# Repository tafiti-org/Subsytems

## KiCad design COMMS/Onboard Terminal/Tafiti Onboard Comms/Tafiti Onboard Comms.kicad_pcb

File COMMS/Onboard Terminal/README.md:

# Tafiti Onboard Communication System

This is the PCB design of the Onboard communication system.

## Components
- STM32H743VIT6
- 2 x sx1278 Ra-02
- SD card module
- 2 x LEDs
- Switch

## Interfaces
- SDMMC
- CAN
- 2 x SPI
- JTAG

## Power Budget

## Schematic

## PCB layout

## 3D PCB Model

## Tools
- STM32CubeIDE
- KiCad

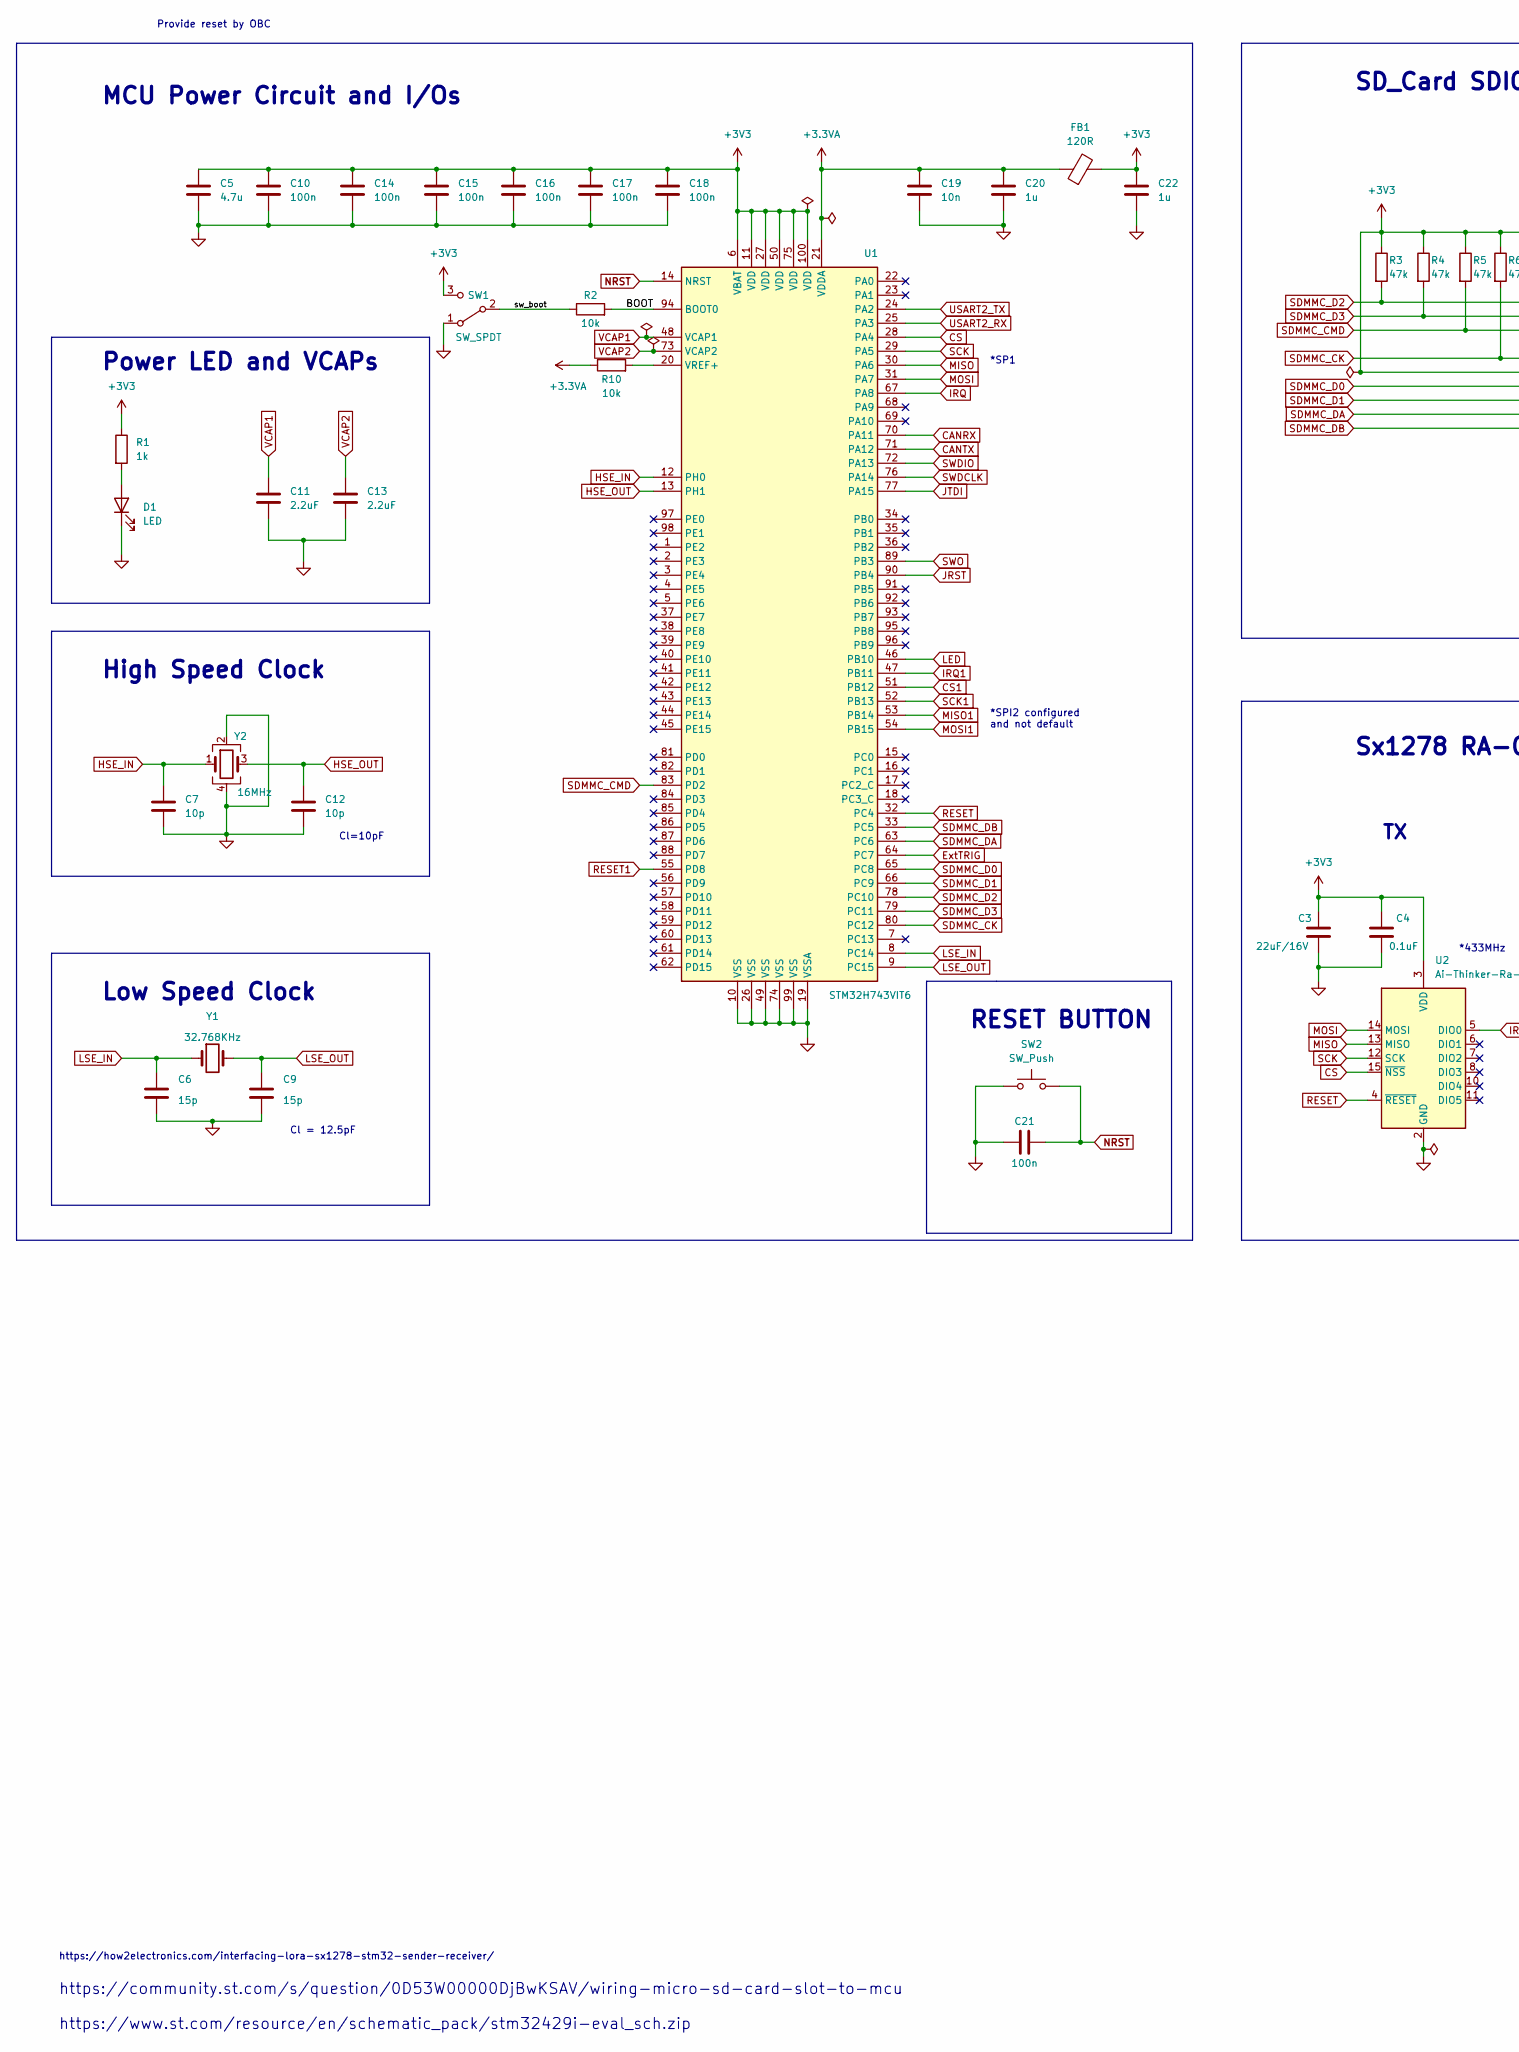
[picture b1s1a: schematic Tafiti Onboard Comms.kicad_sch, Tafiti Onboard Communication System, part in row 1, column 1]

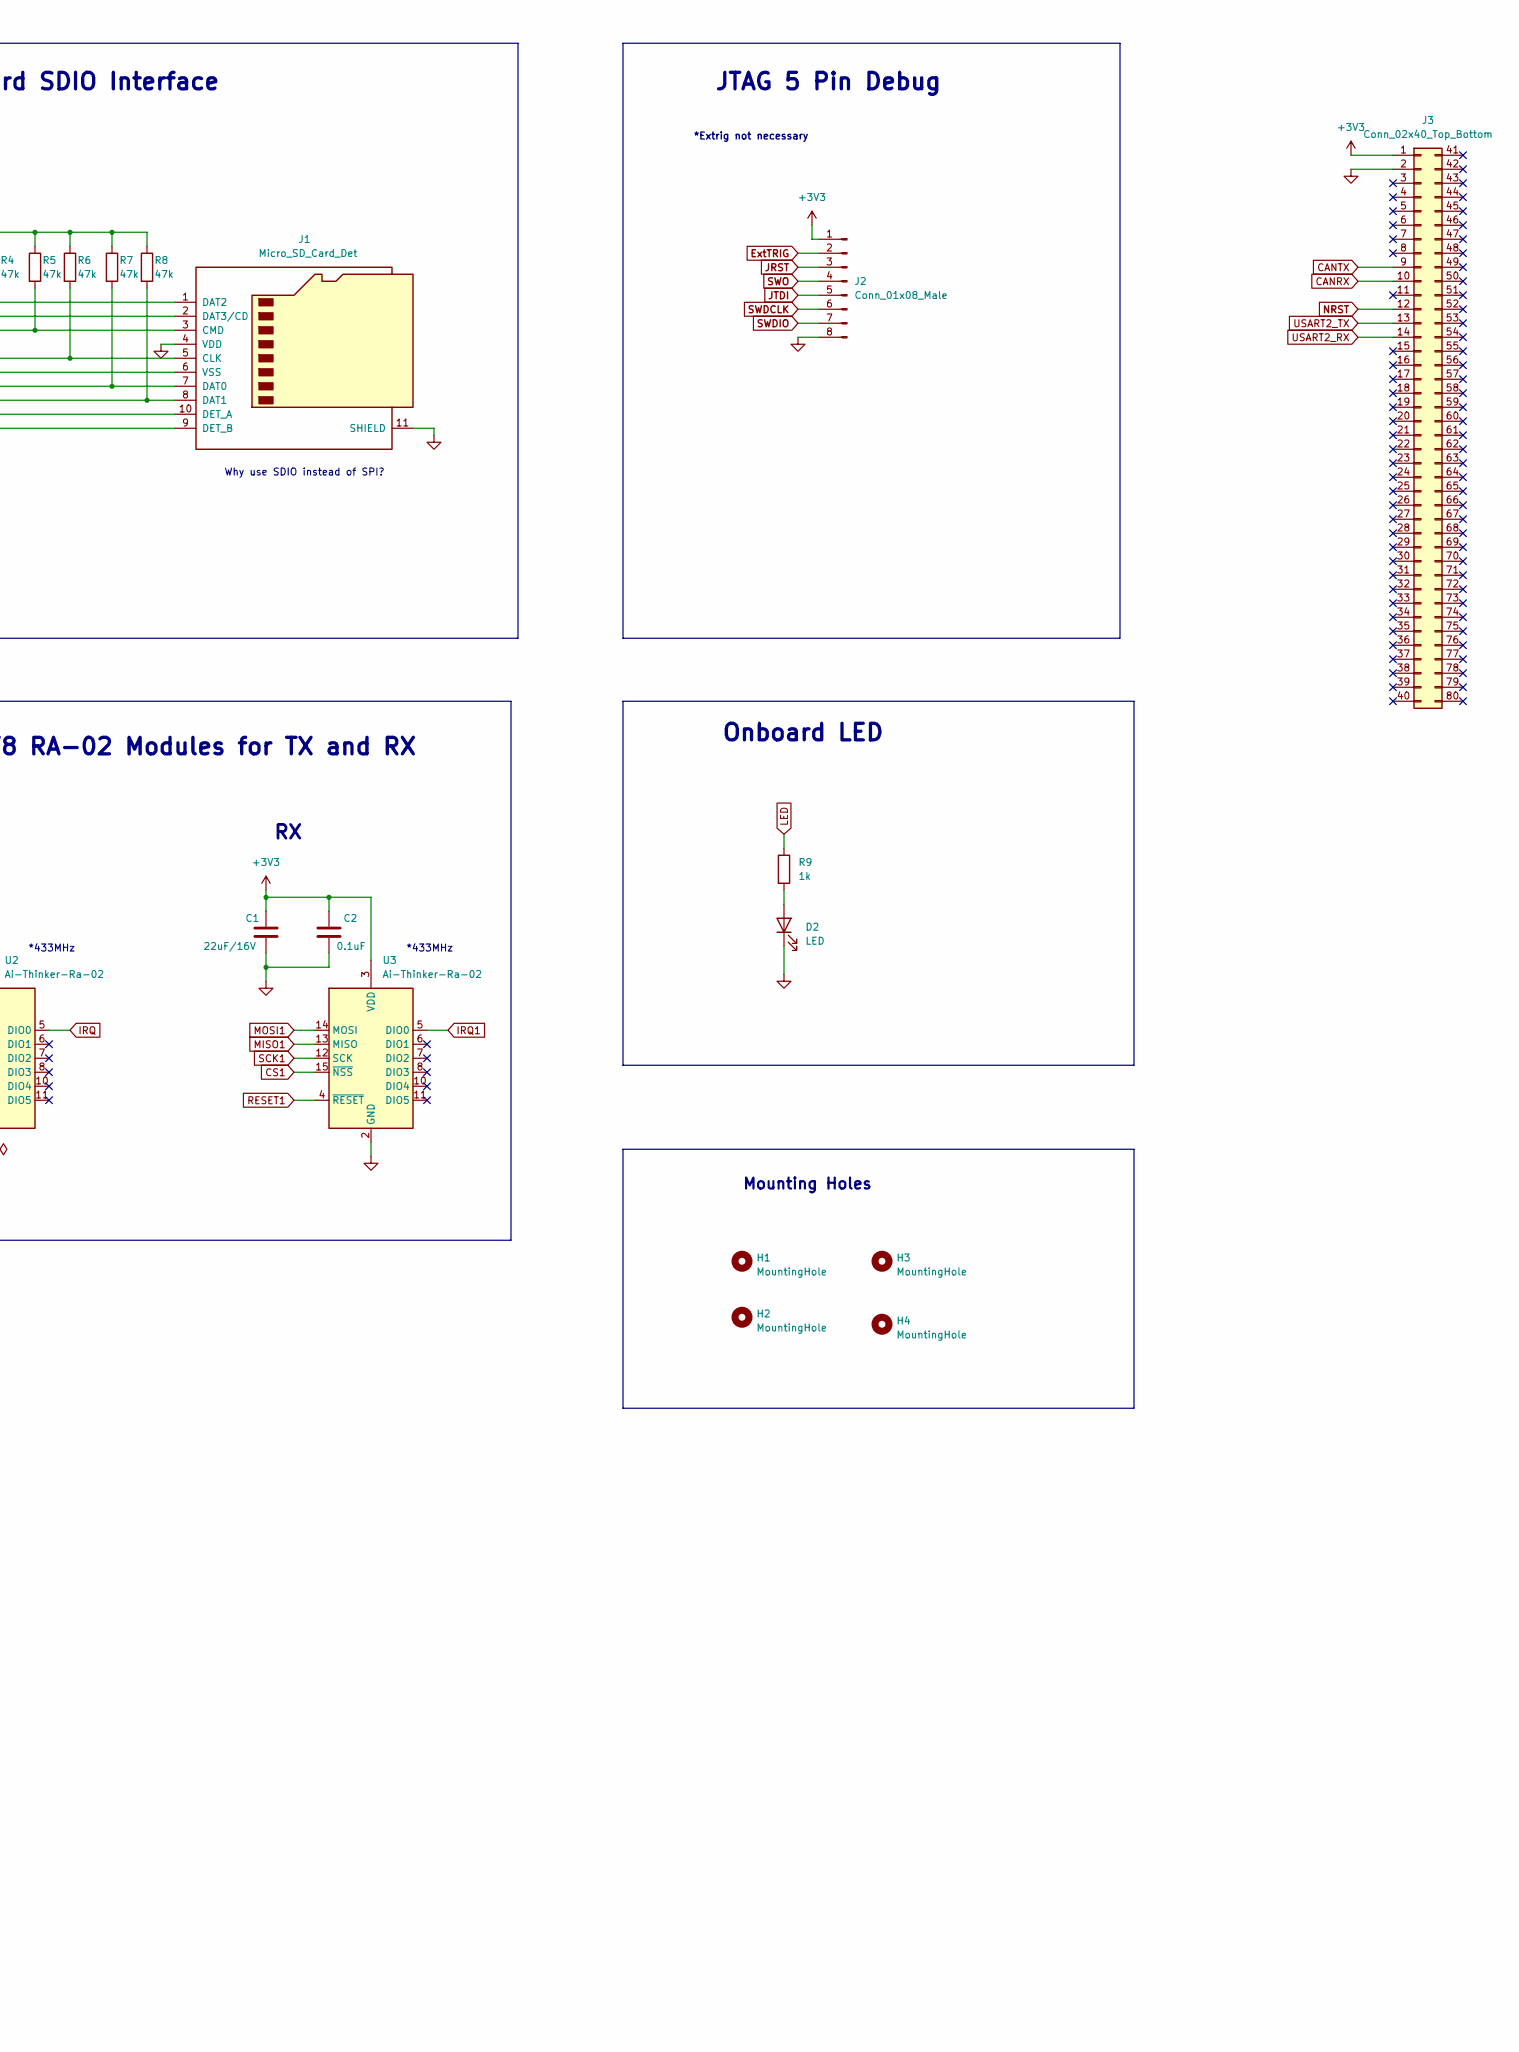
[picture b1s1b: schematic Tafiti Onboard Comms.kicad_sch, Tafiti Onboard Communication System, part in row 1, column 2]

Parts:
C1, C3: 22uF/16V; C_0603_1608Metric
C2, C4: 0.1uF; C_0402_1005Metric
C5: 4.7u; C_0603_1608Metric
C6, C9: 15p; C_0402_1005Metric
C7, C12: 10p; C_0402_1005Metric
C10, C14, C15, C16, C17, C18, C21: 100n; C_0402_1005Metric
C11: 2.2uF; C_0402_1005Metric
C13: 2.2uF; C_0603_1608Metric
C19: 10n; C_0402_1005Metric
C20, C22: 1u; C_0402_1005Metric
D1, D2: LED; LED_0603_1608Metric
FB1: 120R; L_0603_1608Metric
H1, H2, H3, H4: MountingHole
J1: Micro_SD_Card_Det; microSD_HC_Hirose_DM3D-SF
J2: Conn_01x08_Male; PinHeader_1x08_P2.54mm_Vertical
J3: Conn_02x40_Top_Bottom; PinSocket_2x40_P2.54mm_Vertical
R1, R9: 1k; R_0402_1005Metric
R2, R10: 10k; R_0402_1005Metric
R3, R4, R5, R6, R7, R8: 47k; R_0402_1005Metric
SW1: SW_SPDT; SW_E-Switch_EG1224_SPDT_Angled
SW2: SW_Push; SW_PUSH_6mm
U1: STM32H743VIT6; LQFP-100_14x14mm_P0.5mm
U2, U3: Ai-Thinker-Ra-02; Ai-Thinker-Ra-01-LoRa
Y1: 32.768KHz; Crystal_SMD_2012-2Pin_2.0x1.2mm
Y2: 16MHz; Crystal_SMD_3225-4Pin_3.2x2.5mm

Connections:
+3.3VA: C19.1, C20.1, FB1.1, R10.1, U1.21 (VDDA)
+3V3: C1.1, C2.1, C3.1, C4.1, C5.1, C10.1, C14.1, C15.1, C16.1, C17.1, C18.1, C22.1, FB1.2, J1.6 (VSS), J2.1, J3.1, R1.1, R3.1, R4.1, R5.1, R6.1, R7.1, R8.1, SW1.3 (C), U1.6 (VBAT), U1.11 (VDD), U1.27 (VDD), U1.50 (VDD), U1.75 (VDD), U1.100 (VDD), U2.3 (VDD), U3.3 (VDD)
/BOOT: R2.2, U1.94 (BOOT0)
/sw_boot: R2.1, SW1.2 (B)
CANRX: J3.10, U1.70 (PA11)
CANTX: J3.9, U1.71 (PA12)
CS: U1.28 (PA4), U2.15 (~NSS)
CS1: U1.51 (PB12), U3.15 (~NSS)
ExtTRIG: J2.2, U1.64 (PC7)
GND: C1.2, C2.2, C3.2, C4.2, C5.2, C6.2, C7.2, C9.2, C10.2, C11.2, C12.2, C13.2, C14.2, C15.2, C16.2, C17.2, C18.2, C19.2, C20.2, C21.1, C22.2, D1.1 (K), D2.1 (K), J1.4 (VDD), J1.11 (SHIELD), J2.8, J3.2, SW1.1 (A), SW2.1, U1.10 (VSS), U1.19 (VSSA), U1.26 (VSS), U1.49 (VSS), U1.74 (VSS), U1.99 (VSS), U2.1 (GND), U2.2 (GND), U2.9 (GND), U2.16 (GND), U3.1 (GND), U3.2 (GND), U3.9 (GND), U3.16 (GND), Y2.2, Y2.4
HSE_IN: C7.1, U1.12 (PH0), Y2.1
HSE_OUT: C12.1, U1.13 (PH1), Y2.3
IRQ: U1.67 (PA8), U2.5 (DIO0)
IRQ1: U1.47 (PB11), U3.5 (DIO0)
JRST: J2.3, U1.90 (PB4)
JTDI: J2.5, U1.77 (PA15)
LED: R9.1, U1.46 (PB10)
LSE_IN: C6.1, U1.8 (PC14), Y1.1
LSE_OUT: C9.1, U1.9 (PC15), Y1.2
MISO: U1.30 (PA6), U2.13 (MISO)
MISO1: U1.53 (PB14), U3.13 (MISO)
MOSI: U1.31 (PA7), U2.14 (MOSI)
MOSI1: U1.54 (PB15), U3.14 (MOSI)
NRST: C21.2, J3.12, SW2.2, U1.14 (NRST)
unnamed: D1.2 (A), R1.2
unnamed: D2.2 (A), R9.2
unnamed: R10.2, U1.20 (VREF+)
RESET: U1.32 (PC4), U2.4 (~RESET)
RESET1: U1.55 (PD8), U3.4 (~RESET)
SCK: U1.29 (PA5), U2.12 (SCK)
SCK1: U1.52 (PB13), U3.12 (SCK)
SDMMC_CK: J1.5 (CLK), R6.2, U1.80 (PC12)
SDMMC_CMD: J1.3 (CMD), R5.2, U1.83 (PD2)
SDMMC_D0: J1.7 (DAT0), R7.2, U1.65 (PC8)
SDMMC_D1: J1.8 (DAT1), R8.2, U1.66 (PC9)
SDMMC_D2: J1.1 (DAT2), R3.2, U1.78 (PC10)
SDMMC_D3: J1.2 (DAT3/CD), R4.2, U1.79 (PC11)
SDMMC_DA: J1.10 (DET_A), U1.63 (PC6)
SDMMC_DB: J1.9 (DET_B), U1.33 (PC5)
SWDCLK: J2.6, U1.76 (PA14)
SWDIO: J2.7, U1.72 (PA13)
SWO: J2.4, U1.89 (PB3)
USART2_RX: J3.14, U1.25 (PA3)
USART2_TX: J3.13, U1.24 (PA2)
VCAP1: C11.1, U1.48 (VCAP1)
VCAP2: C13.1, U1.73 (VCAP2)

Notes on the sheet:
Onboard LED
Cl = 12.5pF
Cl=10pF
https://www.st.com/resource/en/schematic_pack/stm32429i-eval_sch.zip
https://community.st.com/s/question/0D53W00000DjBwKSAV/wiring-micro-sd-card-slot-to-mcu
Mounting Holes
RESET BUTTON
*Extrig not necessary
Sx1278 RA-02 Modules for TX and RX
https://how2electronics.com/interfacing-lora-sx1278-stm32-sender-receiver/
JTAG 5 Pin Debug
*433MHz
Provide reset by OBC
Power LED and VCAPs
High Speed Clock
MCU Power Circuit and I/Os
Why use SDIO instead of SPI?
*SP1
*SPI2 configured and not default
Low Speed Clock
SD_Card SDIO Interface

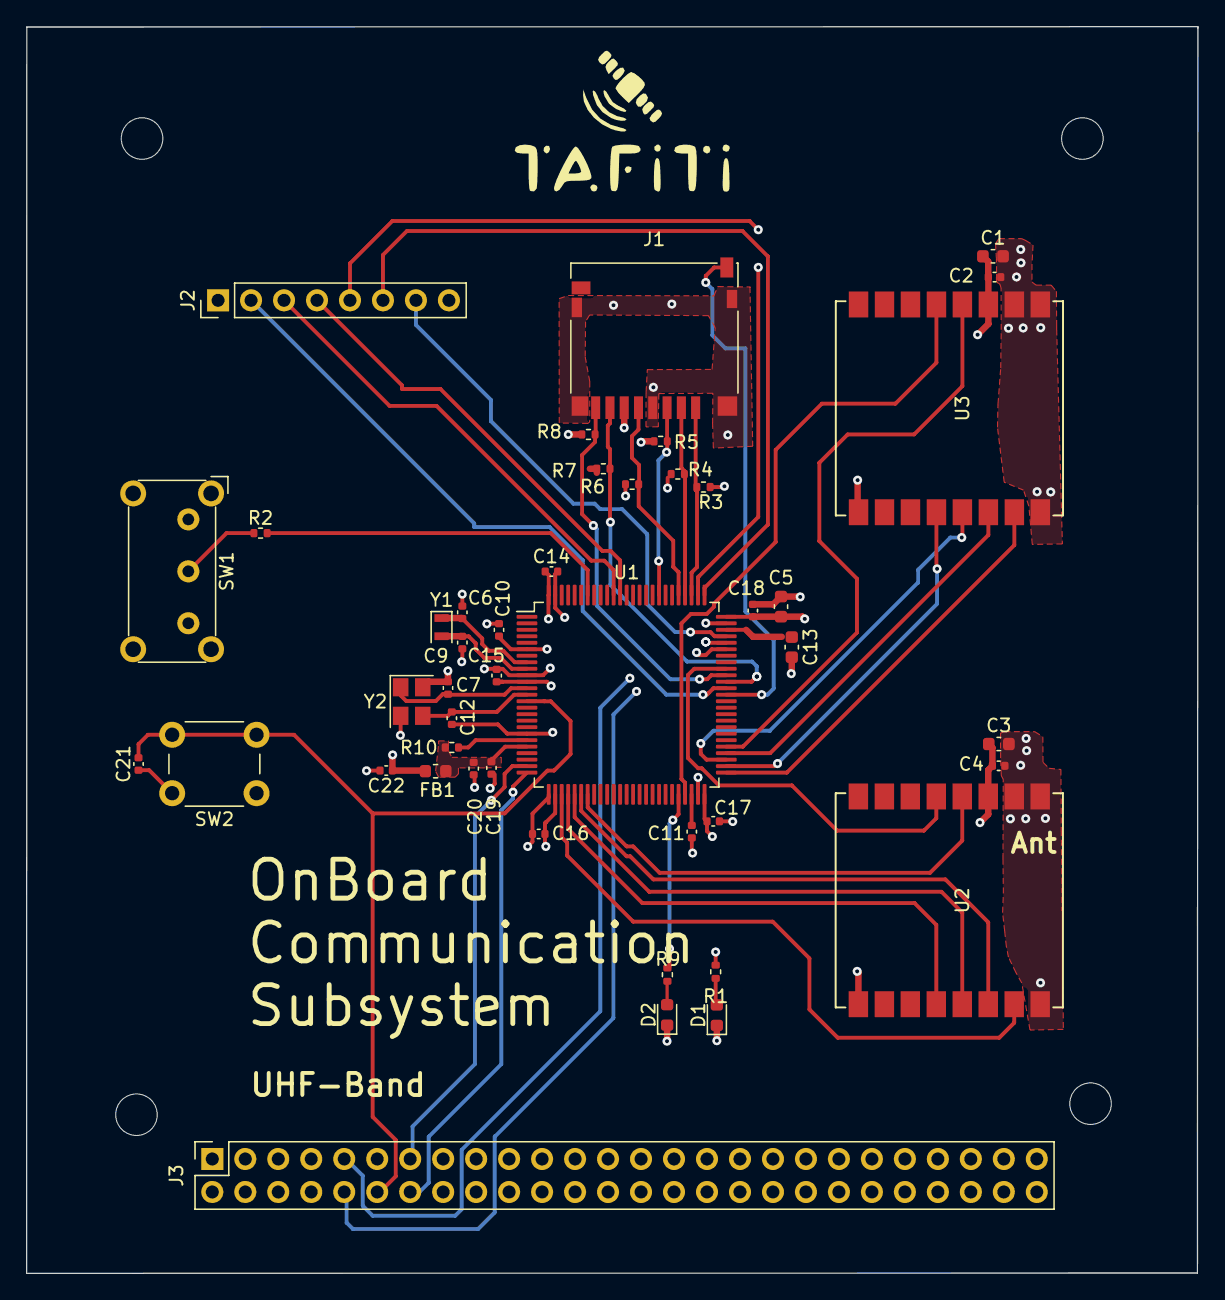
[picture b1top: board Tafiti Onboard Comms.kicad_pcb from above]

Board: 4 copper layers, 90.2 x 96.0 mm, 48 parts (0 on the bottom side), 46 nets.

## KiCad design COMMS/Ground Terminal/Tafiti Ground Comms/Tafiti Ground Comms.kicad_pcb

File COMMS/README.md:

# Tafiti Comms System

This is the repo containing contents of the Tafiti Communication System. This system is built under the sponsorship of the Kenya Space Agency.

## Work Still to be done
- Adding PC104 Connectors and assigned pins from main bus.
- Adding 3D models of the sx1278 Ra-02.
- Adding Logo, Subsytem name, members and more information
- Verify accuracy and requirements fulfilment
- Confirm that the PCB meets the EMC and EMI standards and that it is well designed.

(The above tasks should be done and marked as done beside the task)

## Meet the Team
- Gerald Mbuthia
- Anna kamene
- Martin Kibisu
- Timothy Ndichu
- Ezra Kanana
- Daph Peres

## Purpose

To provide a communication channel to transfer data to and from the Tafiti Nano-satellite.
The data to be transferred includes:
- Image data
- Housekeeping data
- Commands

## Requirements
- Receive housekeeping data from the OBC. This data will effectively be a collection of data from all other subsystems.
- Receive payload data from the Payload subsystem.
- Provide a communication link for the transfer of housekeeping data and payload data from the Cubesat to the 
ground terminal. 
- Provide a link to send telecommands from the ground to the cubesat. This will be a bi-directional communication.
- Provide an interface to view received data and key in commands.
- Allow for data storage onboard the cubesat and on the ground station.
- Provide an API to transfer data over Web.
- Should be portable.
- Data transfer rates should be fast.
- Long range.
## Development procedure

## Software Development

## Testing and Data

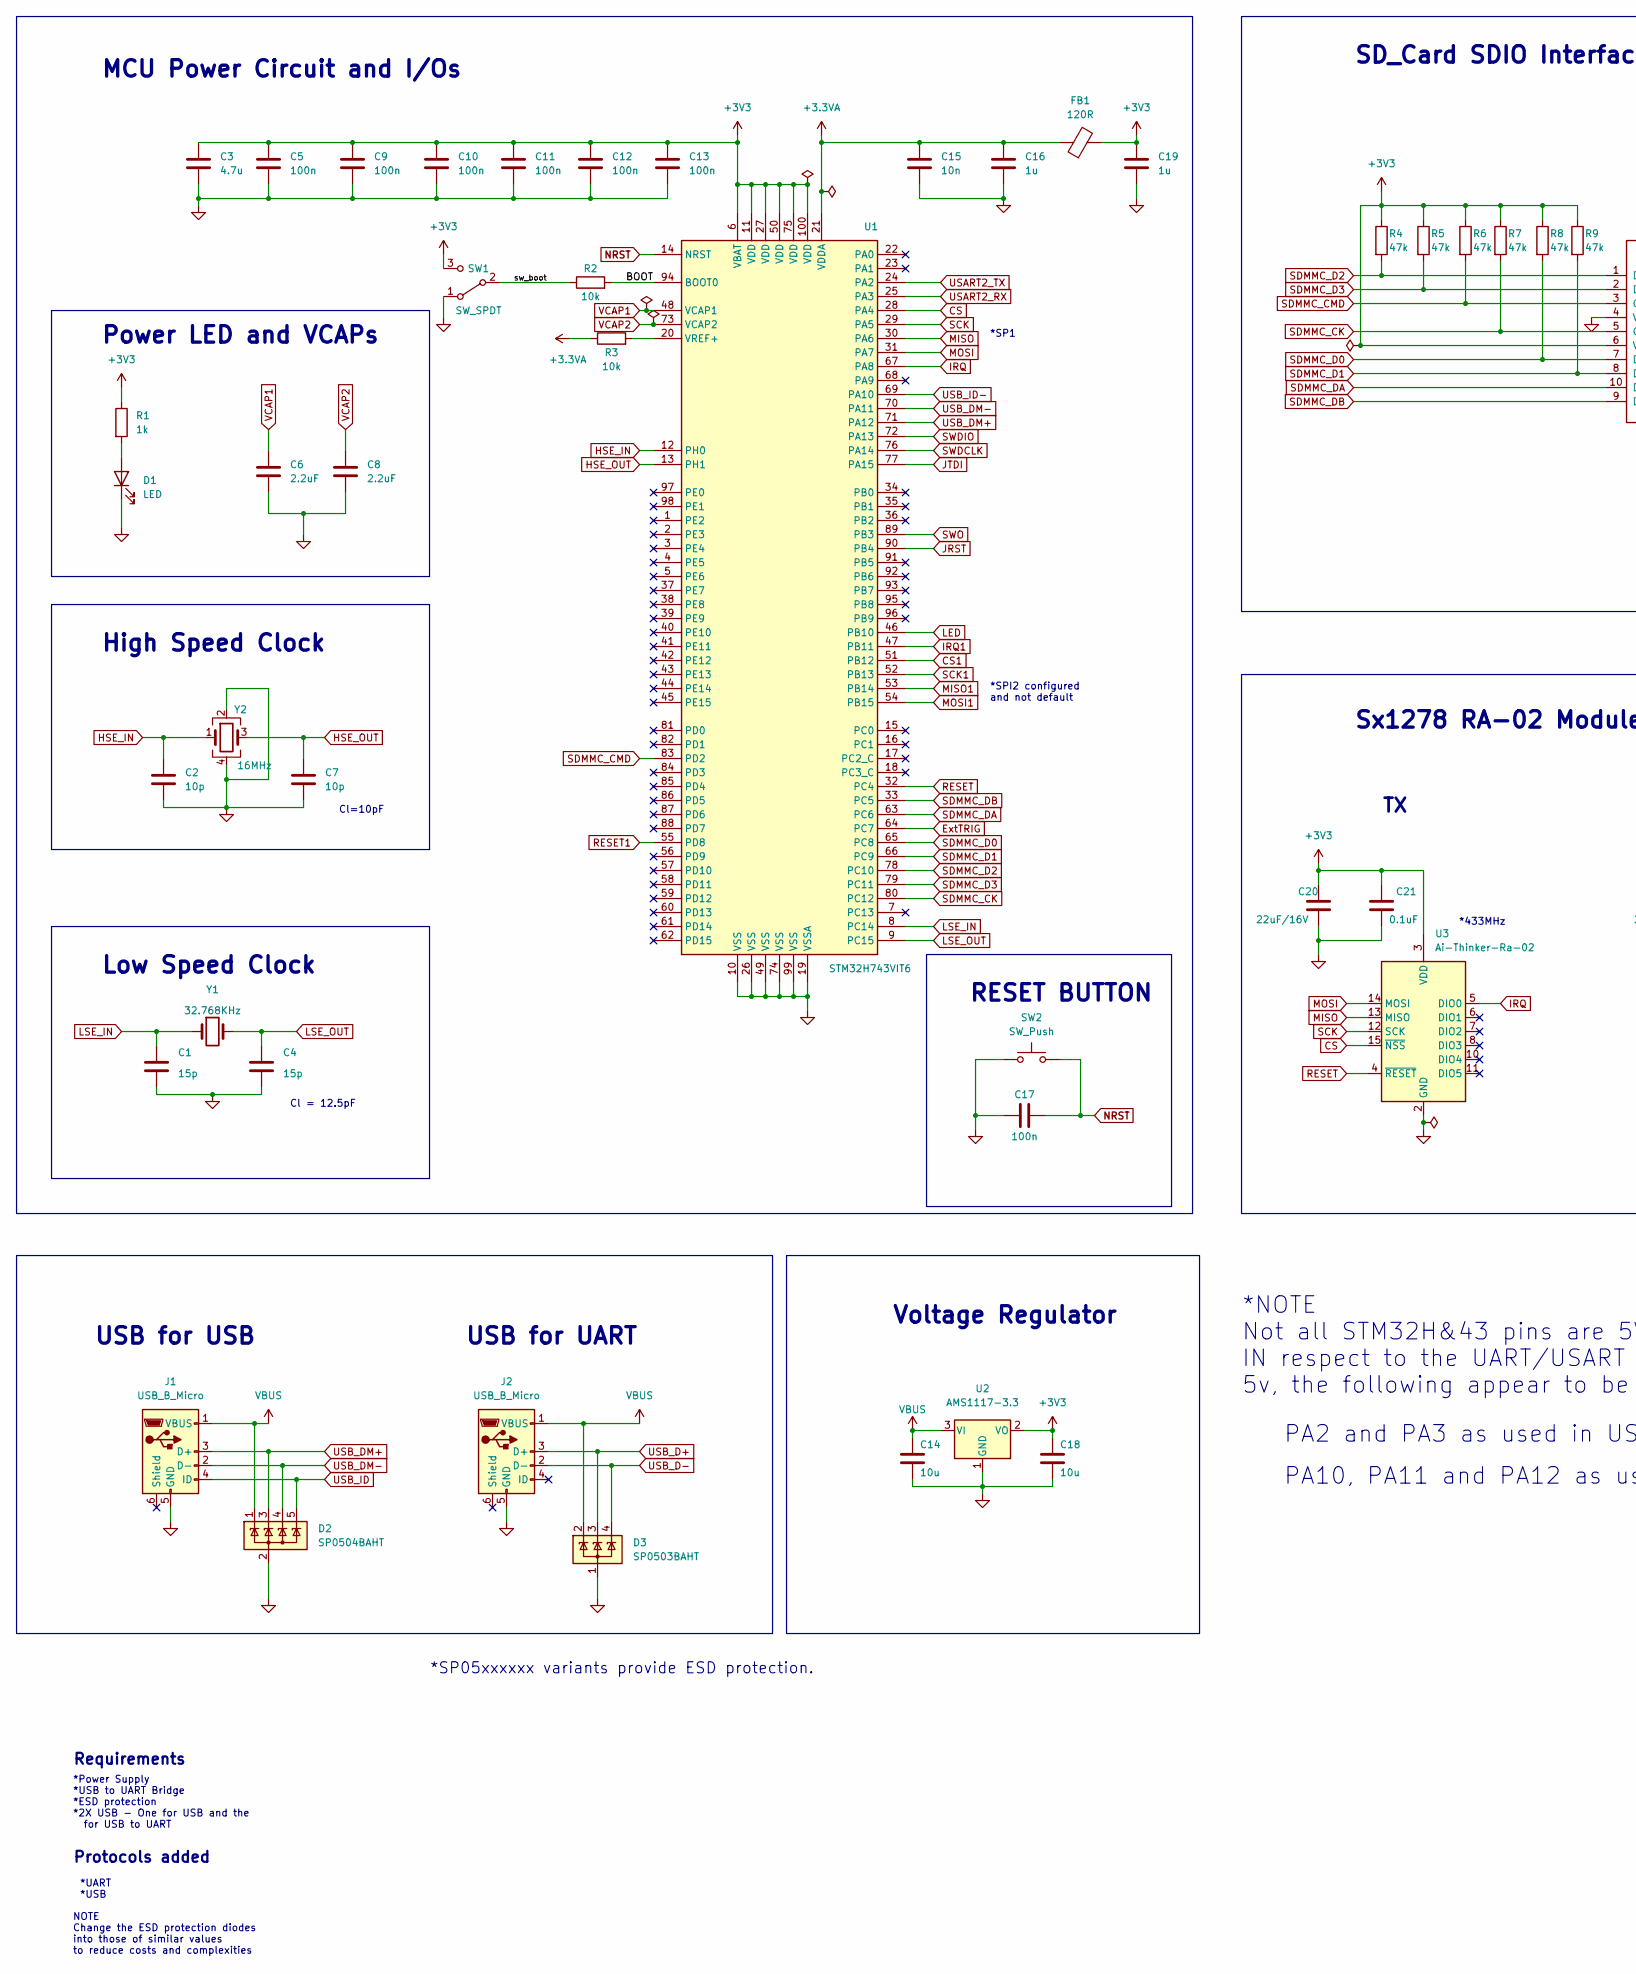
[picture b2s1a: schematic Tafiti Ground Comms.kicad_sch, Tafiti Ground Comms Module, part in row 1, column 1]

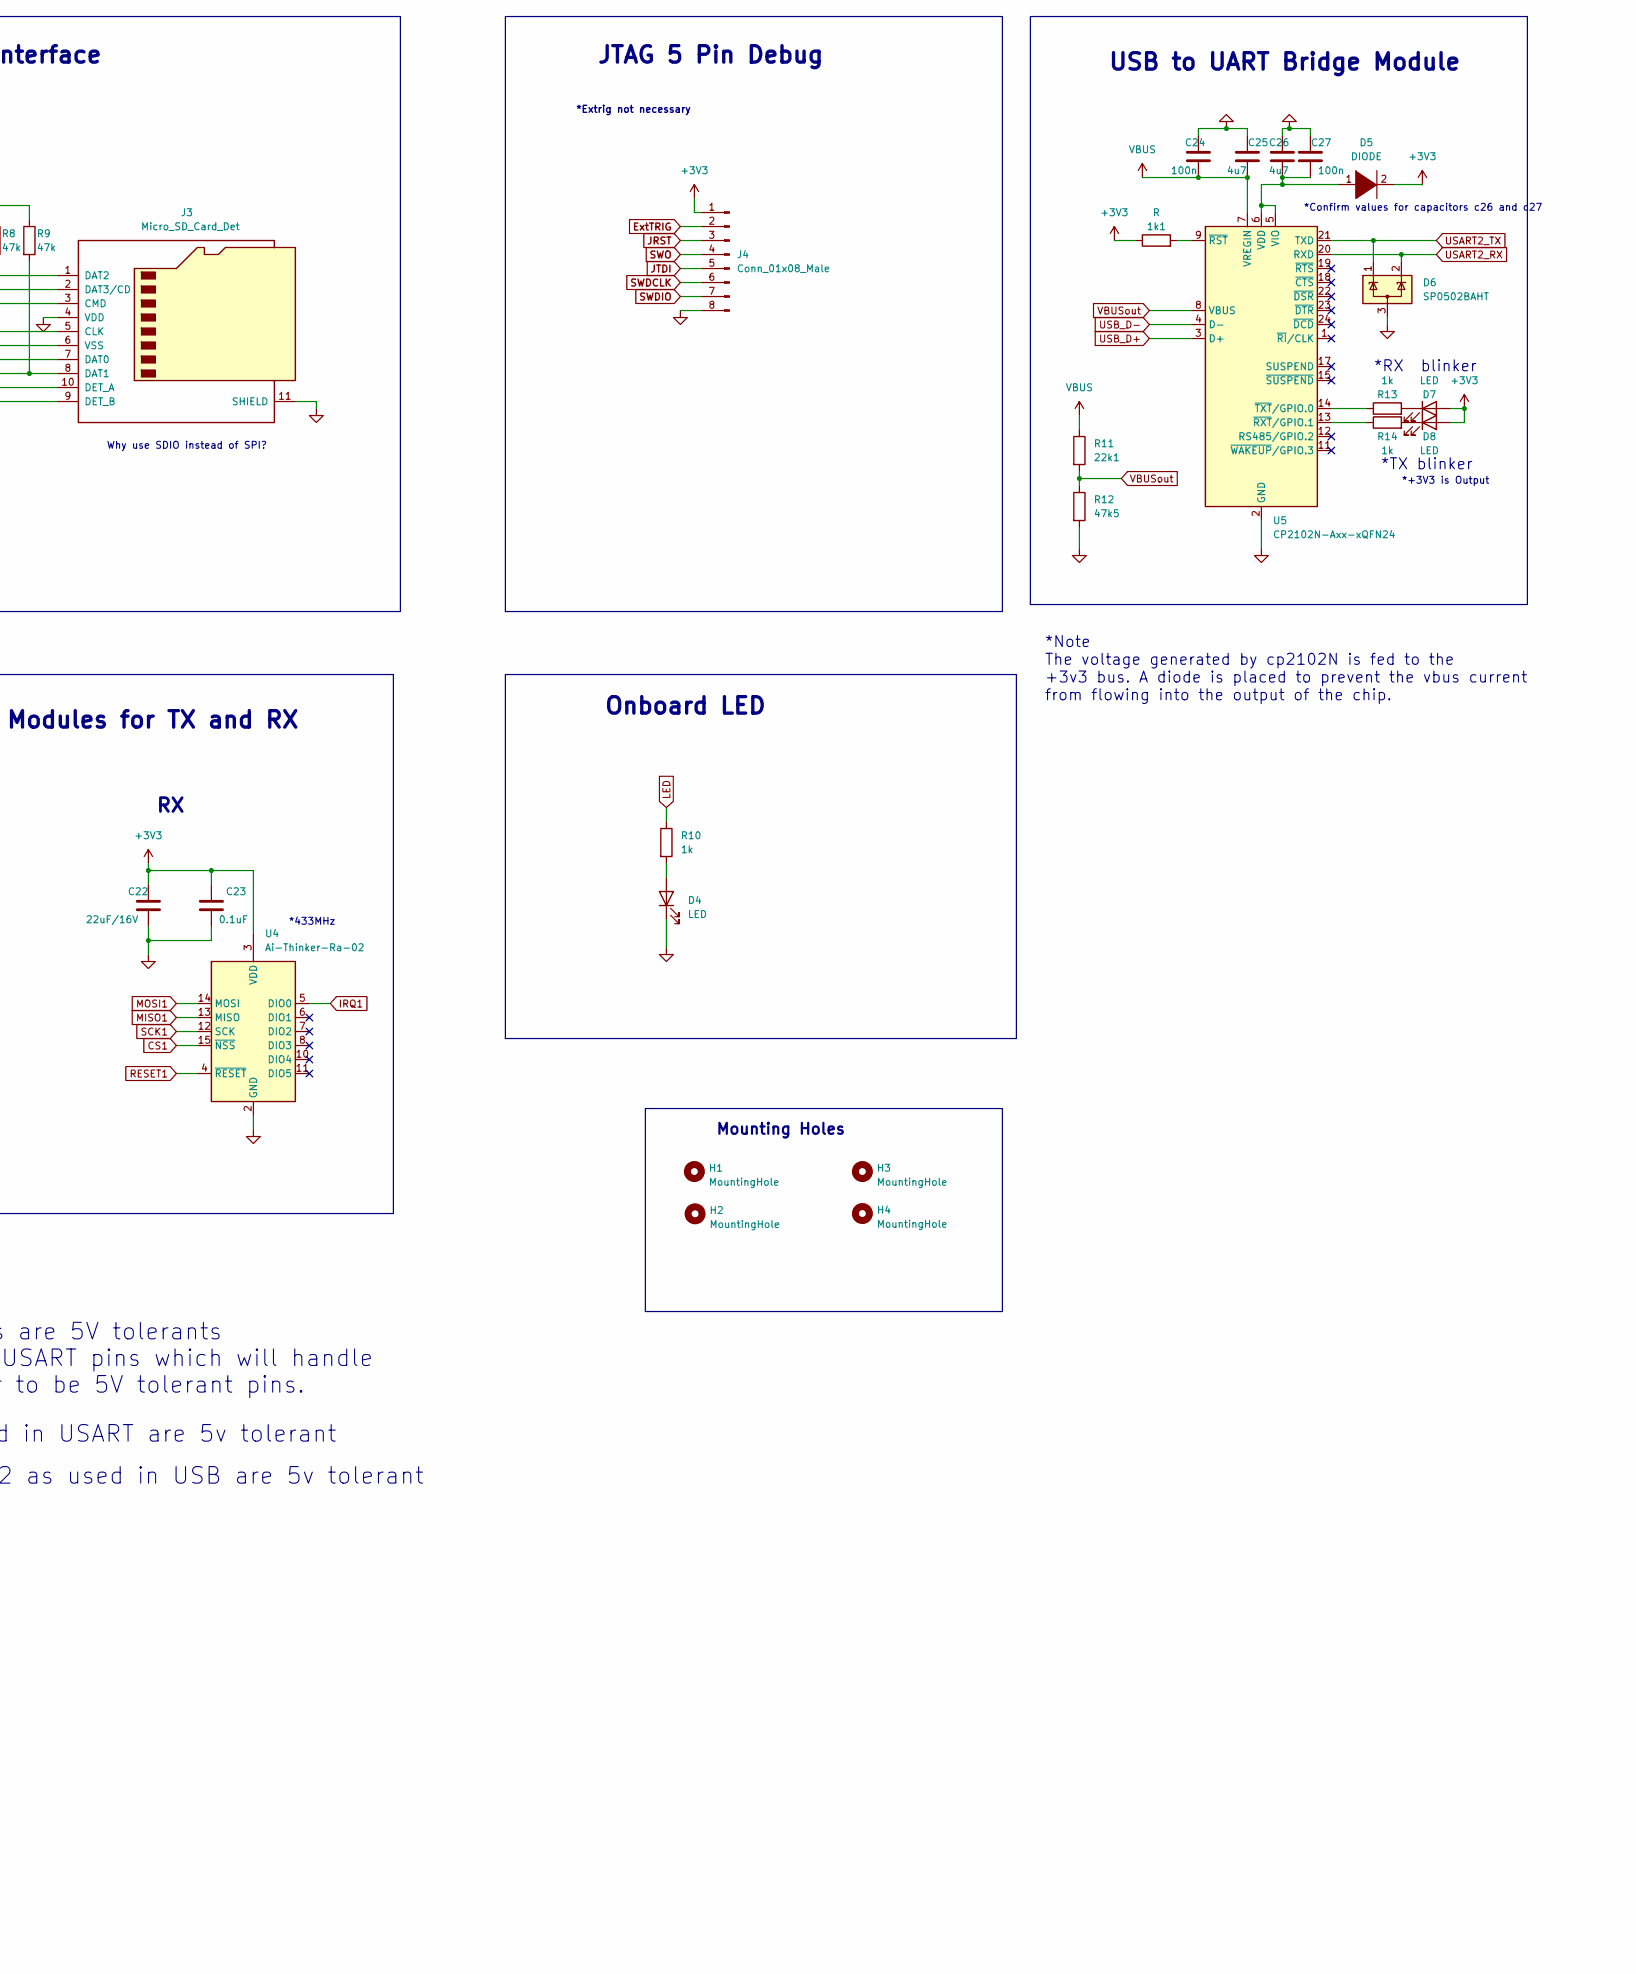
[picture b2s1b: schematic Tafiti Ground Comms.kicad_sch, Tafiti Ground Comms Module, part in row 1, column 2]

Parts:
1k1: R; R_0402_1005Metric
C1, C4: 15p; C_0402_1005Metric
C2, C7: 10p; C_0402_1005Metric
C3: 4.7u; C_0603_1608Metric
C5, C9, C10, C11, C12, C13, C17: 100n; C_0402_1005Metric
C6: 2.2uF; C_0402_1005Metric
C8: 2.2uF; C_0603_1608Metric
C14, C18: 10u; C_0603_1608Metric
C15: 10n; C_0402_1005Metric
C16, C19: 1u; C_0402_1005Metric
C20, C22: 22uF/16V; C_0603_1608Metric
C21, C23: 0.1uF; C_0402_1005Metric
C24, C27: 100n; C_0603_1608Metric
C25, C26: 4u7; C_0603_1608Metric
D1, D4, D7, D8: LED; LED_0603_1608Metric
D2: SP0504BAHT; SOT-23-5
D3: SP0503BAHT; SOT-143
D5: DIODE; D_0603_1608Metric
D6: SP0502BAHT; SOT-23
FB1: 120R; L_0603_1608Metric
H1, H2, H3, H4: MountingHole; MountingHole_3.2mm_M3
J1, J2: USB_B_Micro; USB_Micro-B_Wuerth_629105150521
J3: Micro_SD_Card_Det; microSD_HC_Hirose_DM3D-SF
J4: Conn_01x08_Male; PinHeader_1x08_P2.54mm_Vertical
R1, R10, R13, R14: 1k; R_0402_1005Metric
R2, R3: 10k; R_0402_1005Metric
R4, R5, R6, R7, R8, R9: 47k; R_0402_1005Metric
R11: 22k1; R_0603_1608Metric
R12: 47k5; R_0603_1608Metric
SW1: SW_SPDT; SW_E-Switch_EG1224_SPDT_Angled
SW2: SW_Push; SW_PUSH_6mm
U1: STM32H743VIT6; LQFP-100_14x14mm_P0.5mm
U2: AMS1117-3.3; SOT-223-3_TabPin2
U3, U4: Ai-Thinker-Ra-02; Ai-Thinker-Ra-01-LoRa
U5: CP2102N-Axx-xQFN24; QFN-24-1EP_4x4mm_P0.5mm_EP2.6x2.6mm
Y1: 32.768KHz; Crystal_SMD_2012-2Pin_2.0x1.2mm
Y2: 16MHz; Crystal_SMD_3225-4Pin_3.2x2.5mm

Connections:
+3.3VA: C15.1, C16.1, FB1.1, R3.1, U1.21 (VDDA)
+3V3: 1k1.1, C3.1, C5.1, C9.1, C10.1, C11.1, C12.1, C13.1, C18.1, C19.1, C20.1, C21.1, C22.1, C23.1, D5.2 (A), D7.2 (A), D8.2 (A), FB1.2, J3.6 (VSS), J4.1, R1.1, R4.1, R5.1, R6.1, R7.1, R8.1, R9.1, SW1.3 (C), U1.6 (VBAT), U1.11 (VDD), U1.27 (VDD), U1.50 (VDD), U1.75 (VDD), U1.100 (VDD), U2.2 (VO), U3.3 (VDD), U4.3 (VDD)
/BOOT: R2.2, U1.94 (BOOT0)
/sw_boot: R2.1, SW1.2 (B)
CS: U1.28 (PA4), U3.15 (~NSS)
CS1: U1.51 (PB12), U4.15 (~NSS)
ExtTRIG: J4.2, U1.64 (PC7)
GND: C1.2, C2.2, C3.2, C4.2, C5.2, C6.2, C7.2, C8.2, C9.2, C10.2, C11.2, C12.2, C13.2, C14.2, C15.2, C16.2, C17.1, C18.2, C19.2, C20.2, C21.2, C22.2, C23.2, C24.2, C25.1, C26.2, C27.1, D1.1 (K), D2.2 (A), D3.1 (A), D4.1 (K), D6.3 (A), J1.5 (GND), J2.5 (GND), J3.4 (VDD), J3.11 (SHIELD), J4.8, R12.2, SW1.1 (A), SW2.1, U1.10 (VSS), U1.19 (VSSA), U1.26 (VSS), U1.49 (VSS), U1.74 (VSS), U1.99 (VSS), U2.1 (GND), U3.1 (GND), U3.2 (GND), U3.9 (GND), U3.16 (GND), U4.1 (GND), U4.2 (GND), U4.9 (GND), U4.16 (GND), U5.2 (GND), U5.25 (GND), Y2.2, Y2.4
HSE_IN: C2.1, U1.12 (PH0), Y2.1
HSE_OUT: C7.1, U1.13 (PH1), Y2.3
IRQ: U1.67 (PA8), U3.5 (DIO0)
IRQ1: U1.47 (PB11), U4.5 (DIO0)
JRST: J4.3, U1.90 (PB4)
JTDI: J4.5, U1.77 (PA15)
LED: R10.1, U1.46 (PB10)
LSE_IN: C1.1, U1.8 (PC14), Y1.1
LSE_OUT: C4.1, U1.9 (PC15), Y1.2
MISO: U1.30 (PA6), U3.13 (MISO)
MISO1: U1.53 (PB14), U4.13 (MISO)
MOSI: U1.31 (PA7), U3.14 (MOSI)
MOSI1: U1.54 (PB15), U4.14 (MOSI)
NRST: C17.2, SW2.2, U1.14 (NRST)
unnamed: D1.2 (A), R1.2
unnamed: D4.2 (A), R10.2
unnamed: C26.1, C27.2, D5.1 (K), U5.5 (VIO), U5.6 (VDD)
unnamed: D7.1 (K), R13.2
unnamed: D8.1 (K), R14.2
unnamed: R3.2, U1.20 (VREF+)
unnamed: 1k1.2, U5.9 (~RST)
unnamed: R14.1, U5.13 (~RXT/GPIO.1)
unnamed: R13.1, U5.14 (~TXT/GPIO.0)
RESET: U1.32 (PC4), U3.4 (~RESET)
RESET1: U1.55 (PD8), U4.4 (~RESET)
SCK: U1.29 (PA5), U3.12 (SCK)
SCK1: U1.52 (PB13), U4.12 (SCK)
SDMMC_CK: J3.5 (CLK), R7.2, U1.80 (PC12)
SDMMC_CMD: J3.3 (CMD), R6.2, U1.83 (PD2)
SDMMC_D0: J3.7 (DAT0), R8.2, U1.65 (PC8)
SDMMC_D1: J3.8 (DAT1), R9.2, U1.66 (PC9)
SDMMC_D2: J3.1 (DAT2), R4.2, U1.78 (PC10)
SDMMC_D3: J3.2 (DAT3/CD), R5.2, U1.79 (PC11)
SDMMC_DA: J3.10 (DET_A), U1.63 (PC6)
SDMMC_DB: J3.9 (DET_B), U1.33 (PC5)
SWDCLK: J4.6, U1.76 (PA14)
SWDIO: J4.7, U1.72 (PA13)
SWO: J4.4, U1.89 (PB3)
USART2_RX: D6.2 (K), U1.25 (PA3), U5.20 (RXD)
USART2_TX: D6.1 (K), U1.24 (PA2), U5.21 (TXD)
USB_D+: D3.3 (K), J2.3 (D+), U5.3 (D+)
USB_D-: D3.4 (K), J2.2 (D-), U5.4 (D-)
USB_DM+: D2.3 (K), J1.3 (D+), U1.71 (PA12)
USB_DM-: D2.4 (K), J1.2 (D-), U1.70 (PA11)
USB_ID: D2.5 (K), J1.4 (ID)
USB_ID-: U1.69 (PA10)
VBUS: C14.1, C24.1, C25.2, D2.1 (K), D3.2 (K), J1.1 (VBUS), J2.1 (VBUS), R11.1, U2.3 (VI), U5.7 (VREGIN)
VBUSout: R11.2, R12.1, U5.8 (VBUS)
VCAP1: C6.1, U1.48 (VCAP1)
VCAP2: C8.1, U1.73 (VCAP2)

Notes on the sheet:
High Speed Clock
Sx1278 RA-02 Modules for TX and RX
Requirements
NOTE Change the ESD protection diodes into those of similar values to reduce costs and complexities
*Extrig not necessary
*SPI2 configured and not default
*RX blinker
PA2 and PA3 as used in USART are 5v tolerant
*UART *USB
*+3V3 is Output
*Confirm values for capacitors c26 and c27
MCU Power Circuit and I/Os
*SP1
PA10, PA11 and PA12 as used in USB are 5v tolerant
Why use SDIO instead of SPI?
Protocols added
USB to UART Bridge Module
USB for UART
SD_Card SDIO Interface
Voltage Regulator
*433MHz
*NOTE Not all STM32H&43 pins are 5V tolerants IN respect to the UART/USART pins which will handle 5v, the following appear to be 5V tolerant pins.
Low Speed Clock
JTAG 5 Pin Debug
Mounting Holes
*Note The voltage generated by cp2102N is fed to the +3v3 bus. A diode is placed to prevent the vbus current from flowing into the output of the chip.
*SP05xxxxxx variants provide ESD protection.
Onboard LED
Cl=10pF
Cl = 12.5pF
*TX blinker
RESET BUTTON
Power LED and VCAPs
USB for USB
*Power Supply *USB to UART Bridge *ESD protection *2X USB - One for USB and the for USB to UART

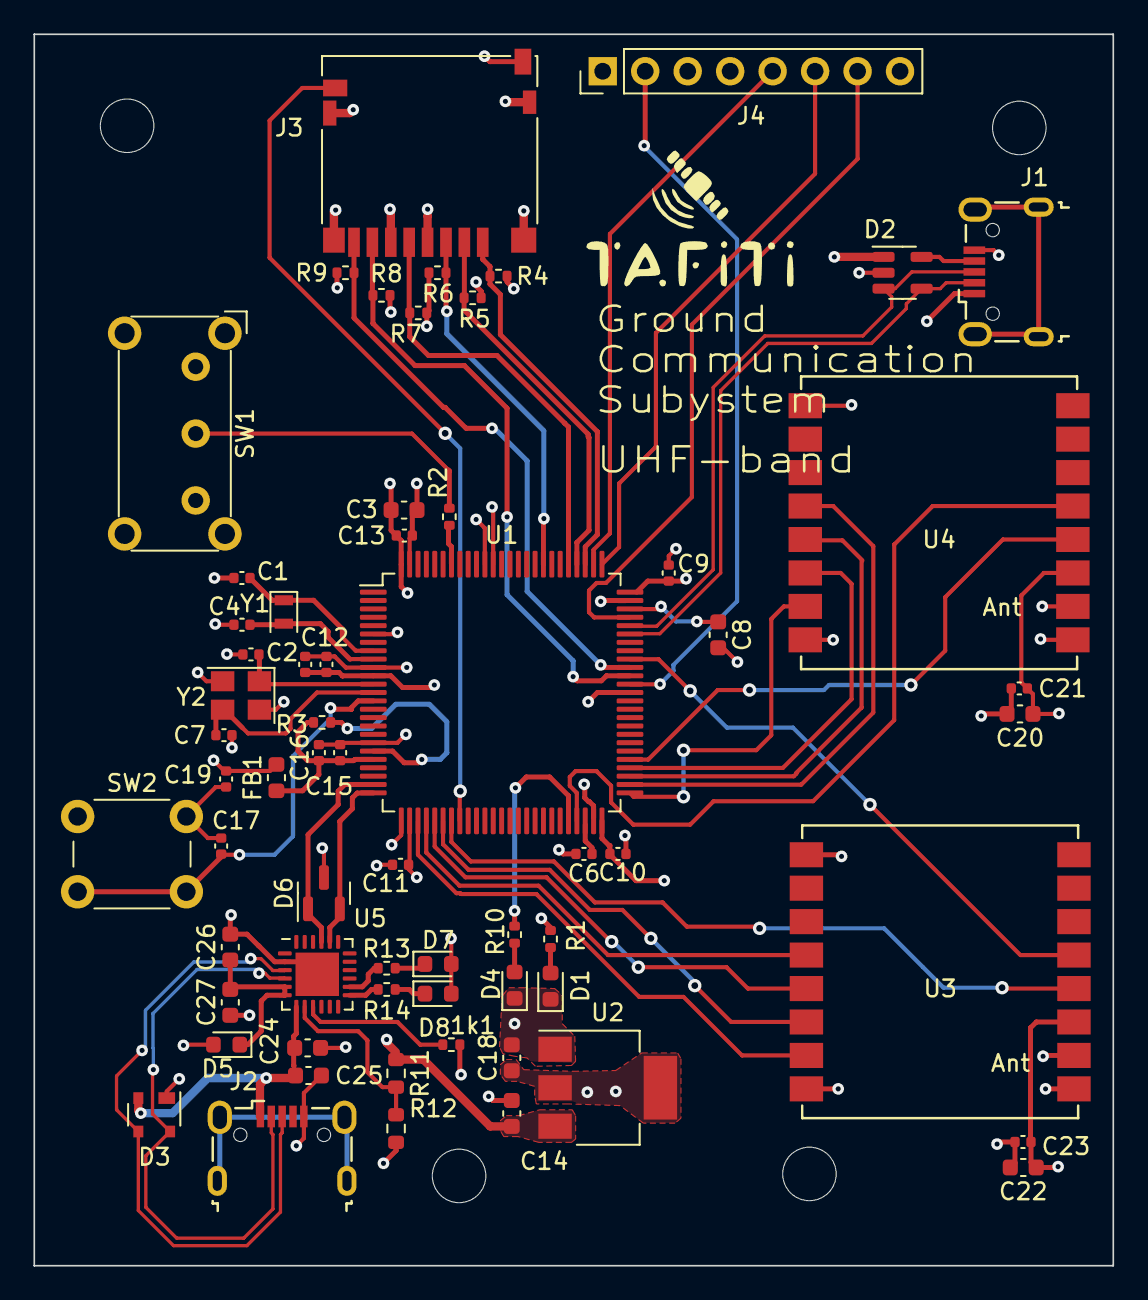
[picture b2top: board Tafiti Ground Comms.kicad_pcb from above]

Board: 4 copper layers, 64.5 x 73.6 mm, 68 parts (0 on the bottom side), 57 nets.

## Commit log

2022-04-07 big bang
2022-04-07 Create LICENSE
2022-04-10 added research reports
2022-05-30 initial reference design commit
2022-06-06 substituted current sensor
    opted for a current sensor with 3V3 supply in favour of the former 5V one.
2022-06-27 updated pcb layout
2023-02-15 TafitiOnboardCommTerminal added
2023-03-05 Added the schematic files of the Tafiti Ground Comms Terminal
2023-03-05 Added Readme content
2023-03-30 Added Ground Terminal files
2023-04-28 Added the Tafiti Ground Terminal
2023-04-28 Added layouts to PCB
2023-04-28 Finished the PCB layout
2023-04-28 Added the models for the USB and Lora Modules as well as the Silkscreen
2023-04-28 Added Lora 3D models as well as Silkscreen
2023-06-14 Added missing 3d models
2023-06-14 Minor changes updated
2023-06-14 Made changes by setting the usb connectors to 1 z offset
2023-06-14 Generated BOM files
2023-08-13 Made minor changes to add mounting holes
2023-09-11 Pushed minor changes so as to delete the repo
2024-04-13 Adding the OBC research paper
2024-04-20 Added EPS design files to the repository
